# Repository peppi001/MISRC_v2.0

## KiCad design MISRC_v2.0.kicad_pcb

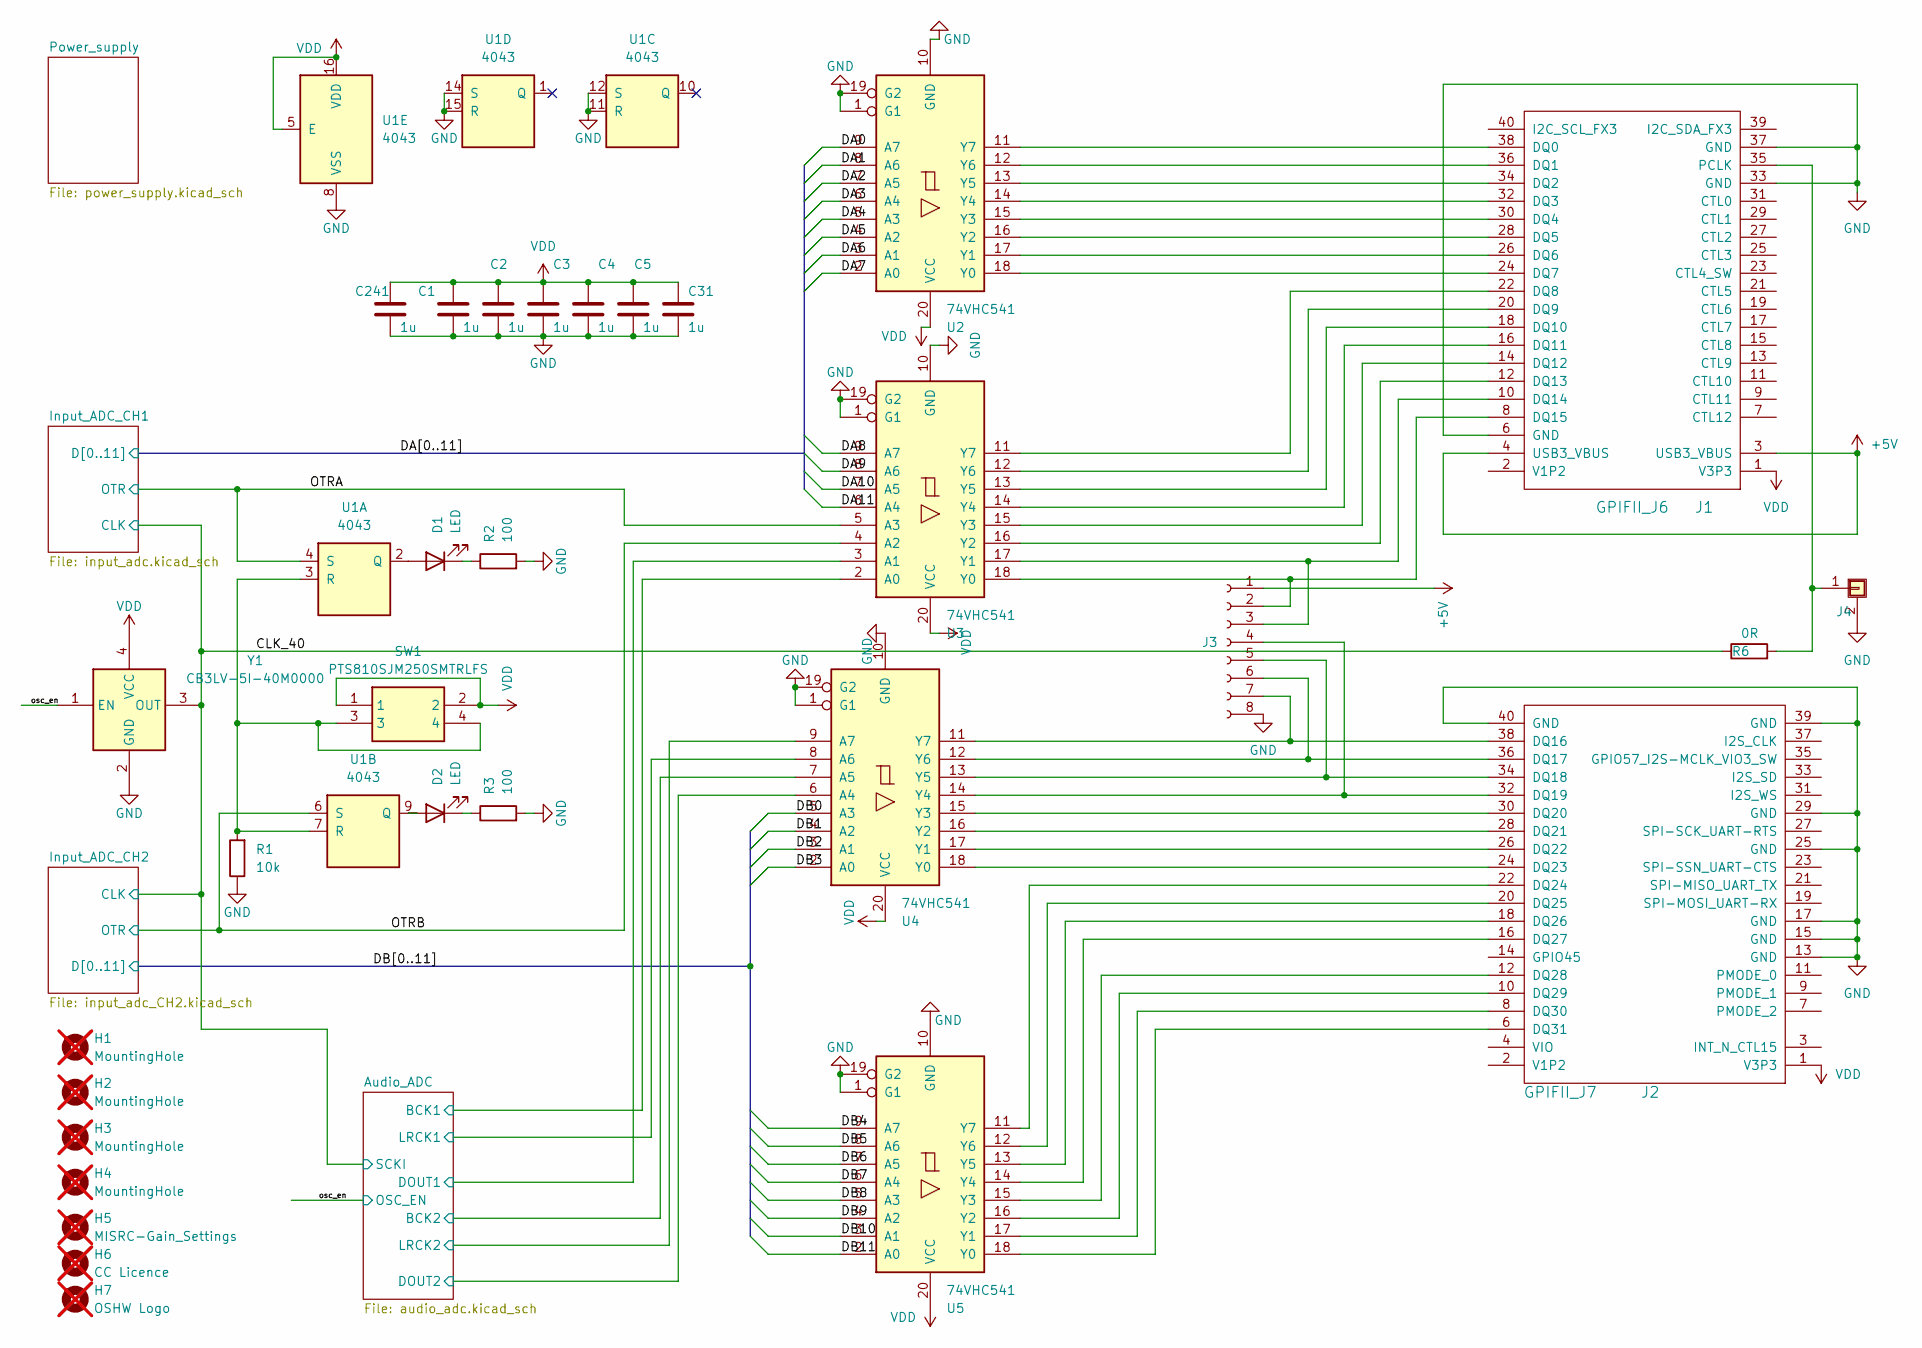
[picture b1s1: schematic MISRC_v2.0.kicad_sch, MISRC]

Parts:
C1, C2, C3, C4, C5, C31, C241: 1u; C_0603_1608Metric; Manufacturer_Part_Number GRM188D71H105KE01D
D1, D2: LED; LED_0805_2012Metric_Pad1.15x1.40mm_HandSolder; Manufacturer_Part_Number APT2012EC
H1, H2, H3, H4: MountingHole; MountingHole_3.2mm_M3; not fitted
H5: MISRC-Gain_Settings; MISRC_gain_settings; not fitted
H6: CC Licence; not fitted
H7: OSHW Logo; OSHW-Logo_5.7x6mm_SilkScreen; not fitted
J1: GPIFII_J6; PinHeader_2x20_P2.54mm_Vertical-1; Manufacturer_Part_Number 61302021121
J2: GPIFII_J7; PinHeader_2x20_P2.54mm_Vertical-1; Manufacturer_Part_Number 61302021121
J3: Conn_01x08_Socket; PinHeader_1x08_P2.54mm_Vertical; Manufacturer_Part_Number 61300811121
J4: Conn_01x01_Shielded; SMA_Amphenol_901-144_Vertical2; Manufacturer_Part_Number RF2-04A-T-00-50-G
R1: 10k; R_0603_1608Metric; Manufacturer_Part_Number RC0603FR-0710KL
R2, R3: 100; R_0603_1608Metric; Manufacturer_Part_Number RC0603FR-07100RL
R6: 0R; R_0603_1608Metric; Manufacturer_Part_Number RC0603FR-070RL
SW1: PTS810SJM250SMTRLFS; PTS810SJG250SMTRLFS; Mouser Part Number 611-PTS810SJM250SMTR
U1: 4043; SO-16_3.9x9.9mm_P1.27mm; Manufacturer_Part_Number HEF4043BT-Q100J
U2, U3, U4, U5: 74VHC541; SOIC-20W_7.5x12.8mm_P1.27mm; Manufacturer_Part_Number 74VHC541D,118
Y1: CB3LV-5I-40M0000; CB3LV5I40M0000; Mouser Part Number 774-CB3LV-5I-40M0000

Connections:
+5V: J1.3 (USB3_VBUS), J1.4 (USB3_VBUS), J3.1; also elsewhere on the board
/Audio_ADC/BCK1: U3.2 (A0); also elsewhere on the board
/Audio_ADC/BCK2: U4.7 (A5); also elsewhere on the board
/Audio_ADC/DOUT1: U3.3 (A1); also elsewhere on the board
/Audio_ADC/DOUT2: U4.6 (A4); also elsewhere on the board
/Audio_ADC/LRCK1: U4.8 (A6); also elsewhere on the board
/Audio_ADC/LRCK2: U4.9 (A7); also elsewhere on the board
/CLK_40: R6.1, Y1.3 (OUT); also elsewhere on the board
/DA0: U2.9 (A7); also elsewhere on the board
/DA1: U2.8 (A6); also elsewhere on the board
/DA2: U2.7 (A5); also elsewhere on the board
/DA3: U2.6 (A4); also elsewhere on the board
/DA4: U2.5 (A3); also elsewhere on the board
/DA5: U2.4 (A2); also elsewhere on the board
/DA6: U2.3 (A1); also elsewhere on the board
/DA7: U2.2 (A0); also elsewhere on the board
/DA8: U3.9 (A7); also elsewhere on the board
/DA9: U3.8 (A6); also elsewhere on the board
/DA10: U3.7 (A5); also elsewhere on the board
/DA11: U3.6 (A4); also elsewhere on the board
/DB0: U4.5 (A3); also elsewhere on the board
/DB1: U4.4 (A2); also elsewhere on the board
/DB2: U4.3 (A1); also elsewhere on the board
/DB3: U4.2 (A0); also elsewhere on the board
/DB4: U5.9 (A7); also elsewhere on the board
/DB5: U5.8 (A6); also elsewhere on the board
/DB6: U5.7 (A5); also elsewhere on the board
/DB7: U5.6 (A4); also elsewhere on the board
/DB8: U5.5 (A3); also elsewhere on the board
/DB9: U5.4 (A2); also elsewhere on the board
/DB10: U5.3 (A1); also elsewhere on the board
/DB11: U5.2 (A0); also elsewhere on the board
/OTRA: U1.4 (S), U3.5 (A3); also elsewhere on the board
/OTRB: U1.6 (S), U3.4 (A2); also elsewhere on the board
/osc_en: Y1.1 (EN); also elsewhere on the board
GND: C1.2, C2.2, C3.2, C4.2, C5.2, C31.2, C241.2, J1.6 (GND), J1.33 (GND), J1.37 (GND), J2.13 (GND), J2.15 (GND), J2.17 (GND), J2.25 (GND), J2.29 (GND), J2.39 (GND), J2.40 (GND), J3.8, J4.2 (Shield), R1.1, R2.2, R3.2, U1.8 (VSS), U1.11 (R), U1.12 (S), U1.14 (S), U1.15 (R), U2.1 (G1), U2.10 (GND), U2.19 (G2), U3.1 (G1), U3.10 (GND), U3.19 (G2), U4.1 (G1), U4.10 (GND), U4.19 (G2), U5.1 (G1), U5.10 (GND), U5.19 (G2), Y1.2 (GND); also elsewhere on the board
unnamed: D1.2 (A), U1.2 (Q)
unnamed: D1.1 (K), R2.1
unnamed: D2.2 (A), U1.9 (Q)
unnamed: D2.1 (K), R3.1
unnamed: J1.38 (DQ0), U2.11 (Y7)
unnamed: J1.36 (DQ1), U2.12 (Y6)
unnamed: J1.34 (DQ2), U2.13 (Y5)
unnamed: J1.32 (DQ3), U2.14 (Y4)
unnamed: J1.30 (DQ4), U2.15 (Y3)
unnamed: J1.28 (DQ5), U2.16 (Y2)
unnamed: J1.26 (DQ6), U2.17 (Y1)
unnamed: J1.24 (DQ7), U2.18 (Y0)
unnamed: J1.22 (DQ8), U3.11 (Y7)
unnamed: J1.20 (DQ9), U3.12 (Y6)
unnamed: J1.18 (DQ10), U3.13 (Y5)
unnamed: J1.16 (DQ11), U3.14 (Y4)
unnamed: J1.14 (DQ12), U3.15 (Y3)
unnamed: J1.12 (DQ13), U3.16 (Y2)
unnamed: J1.10 (DQ14), J3.3, U3.17 (Y1)
unnamed: J1.8 (DQ15), J3.2, U3.18 (Y0)
unnamed: J1.35 (PCLK), J4.1, R6.2
unnamed: J2.38 (DQ16), J3.7, U4.11 (Y7)
unnamed: J2.36 (DQ17), J3.6, U4.12 (Y6)
unnamed: J2.34 (DQ18), J3.5, U4.13 (Y5)
unnamed: J2.32 (DQ19), J3.4, U4.14 (Y4)
unnamed: J2.30 (DQ20), U4.15 (Y3)
unnamed: J2.28 (DQ21), U4.16 (Y2)
unnamed: J2.26 (DQ22), U4.17 (Y1)
unnamed: J2.24 (DQ23), U4.18 (Y0)
unnamed: J2.22 (DQ24), U5.11 (Y7)
unnamed: J2.20 (DQ25), U5.12 (Y6)
unnamed: J2.18 (DQ26), U5.13 (Y5)
unnamed: J2.16 (DQ27), U5.14 (Y4)
unnamed: J2.12 (DQ28), U5.15 (Y3)
unnamed: J2.10 (DQ29), U5.16 (Y2)
unnamed: J2.8 (DQ30), U5.17 (Y1)
unnamed: J2.6 (DQ31), U5.18 (Y0)
unnamed: R1.2, SW1.3, SW1.4, U1.3 (R), U1.7 (R)
VDD: C1.1, C2.1, C3.1, C4.1, C5.1, C31.1, C241.1, J1.1 (V3P3), J2.1 (V3P3), SW1.1, SW1.2, U1.5 (E), U1.16 (VDD), U2.20 (VCC), U3.20 (VCC), U4.20 (VCC), U5.20 (VCC), Y1.4 (VCC); also elsewhere on the board

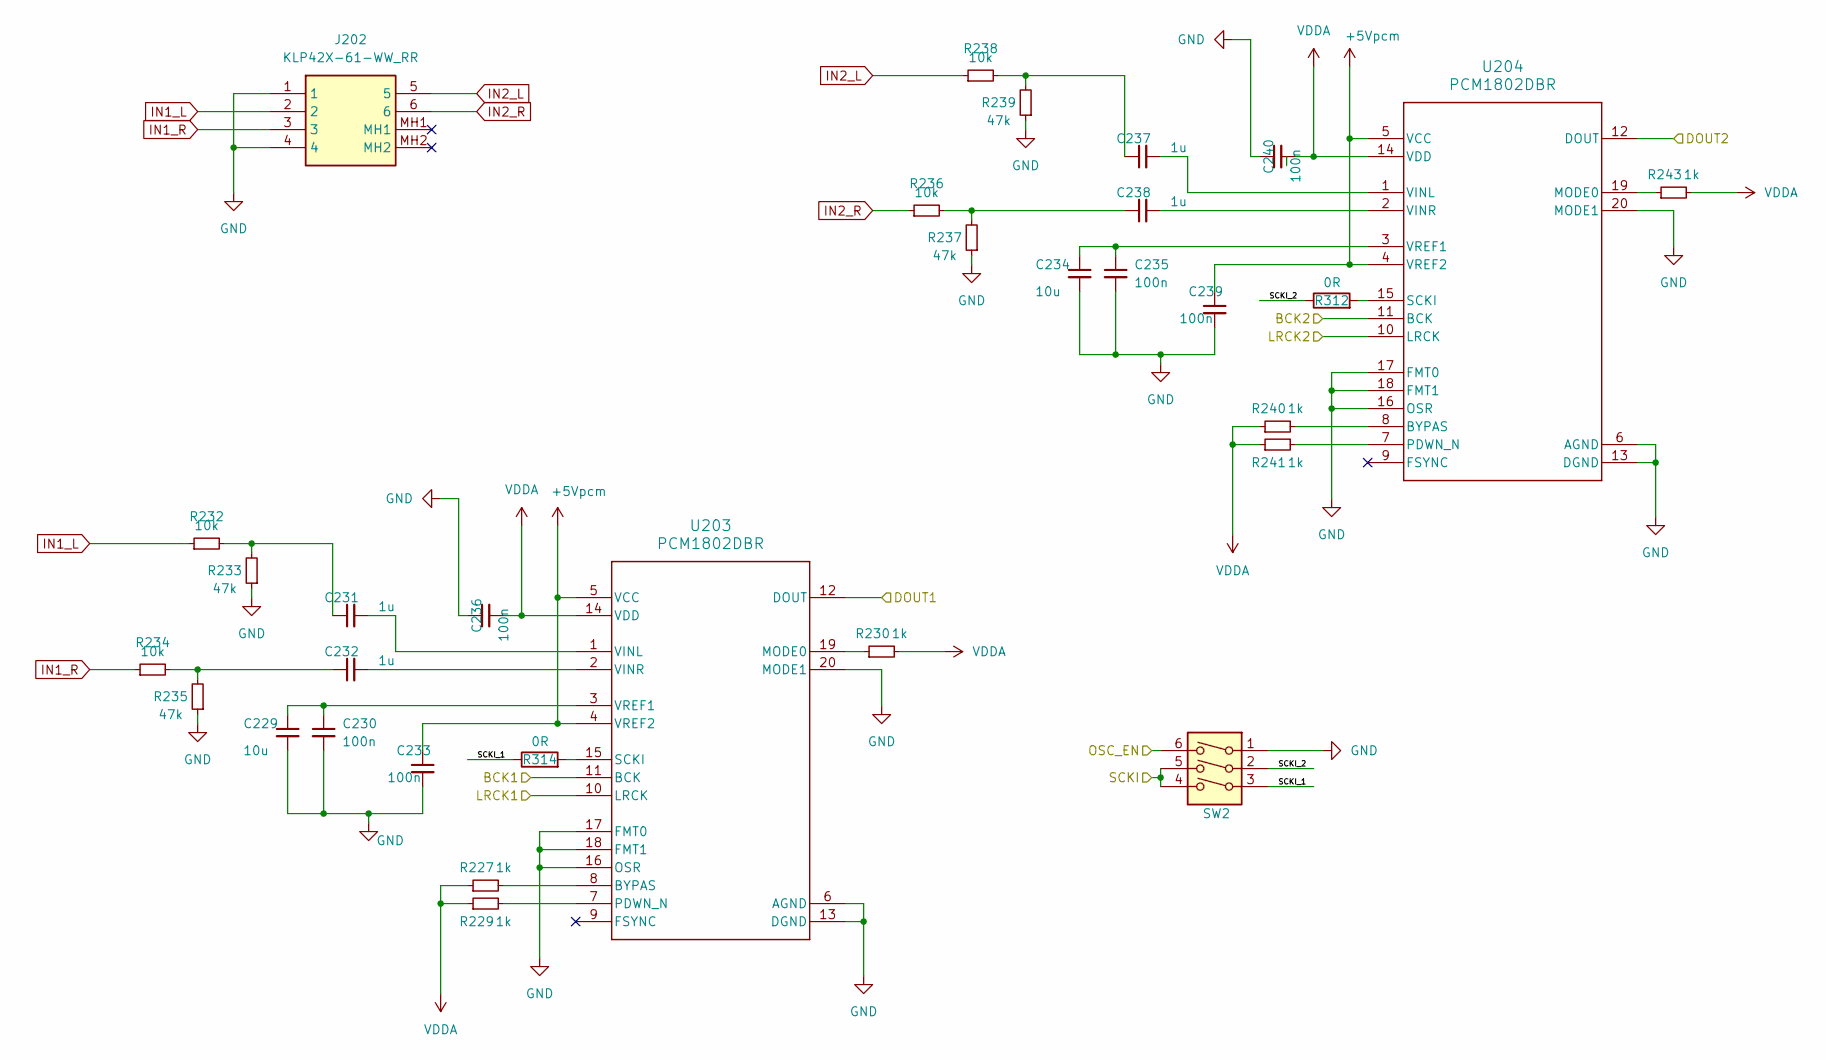
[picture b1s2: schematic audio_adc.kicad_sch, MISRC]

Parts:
C229, C234: 10u; C_0603_1608Metric; Manufacturer_Part_Number GRM188C81C106MA73D
C230, C233, C235, C236, C239, C240: 100n; C_0603_1608Metric; Manufacturer_Part_Number GRM188R72A104KA35D
C231, C232, C237, C238: 1u; C_0603_1608Metric; Manufacturer_Part_Number GRM188D71H105KE01D
J202: KLP42X-61-WW_RR; KLP42X61WWRR; Mouser Part Number 806-KLP42X-61-WWRR
R227, R229, R230, R240, R241, R243: 1k; R_0603_1608Metric; Manufacturer_Part_Number RC0603FR-071KL
R232, R234, R236, R238: 10k; R_0603_1608Metric; Manufacturer_Part_Number RC0603FR-0710KL
R233, R235, R237, R239: 47k; R_0603_1608Metric; Manufacturer_Part_Number RC0603FR-0747KL
R312, R314: 0R; R_0603_1608Metric; Manufacturer_Part_Number RC0603FR-070RL
SW2: SW_DIP_x03; SW_DIP_SPSTx03_Slide_6.7x9.18mm_W8.61mm_P2.54mm_LowProfile; Manufacturer_Part_Number A6S-3104-H
U203, U204: PCM1802DBR; SOP65P780X200-20N; Manufacturer_Part_Number PCM1802DBR

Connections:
+5Vpcm: C233.1, C239.1, U203.4 (VREF2), U203.5 (VCC), U204.4 (VREF2), U204.5 (VCC); also elsewhere on the board
/Audio_ADC/BCK1: U203.11 (BCK); also elsewhere on the board
/Audio_ADC/BCK2: U204.11 (BCK); also elsewhere on the board
/Audio_ADC/DOUT1: U203.12 (DOUT); also elsewhere on the board
/Audio_ADC/DOUT2: U204.12 (DOUT); also elsewhere on the board
/Audio_ADC/LRCK1: U203.10 (LRCK); also elsewhere on the board
/Audio_ADC/LRCK2: U204.10 (LRCK); also elsewhere on the board
/Audio_ADC/SCKI_1: R314.1, SW2.3
/Audio_ADC/SCKI_2: R312.1, SW2.2
/CLK_40: SW2.4, SW2.5; also elsewhere on the board
/osc_en: SW2.6; also elsewhere on the board
GND: C229.2, C230.2, C233.2, C234.2, C235.2, C236.1, C239.2, C240.1, J202.1, J202.4, R233.1, R235.1, R237.1, R239.1, SW2.1, U203.6 (AGND), U203.13 (DGND), U203.16 (OSR), U203.17 (FMT0), U203.18 (FMT1), U203.20 (MODE1), U204.6 (AGND), U204.13 (DGND), U204.16 (OSR), U204.17 (FMT0), U204.18 (FMT1), U204.20 (MODE1); also elsewhere on the board
IN1_L: J202.2, R232.1
IN1_R: J202.3, R234.1
IN2_L: J202.5, R238.1
IN2_R: J202.6, R236.1
unnamed: C231.1, R232.2, R233.2
unnamed: C232.1, R234.2, R235.2
unnamed: C237.1, R238.2, R239.2
unnamed: C238.1, R236.2, R237.2
unnamed: R227.2, U203.8 (BYPAS)
unnamed: R230.1, U203.19 (MODE0)
unnamed: R229.2, U203.7 (PDWN_N)
unnamed: R314.2, U203.15 (SCKI)
unnamed: C231.2, U203.1 (VINL)
unnamed: C232.2, U203.2 (VINR)
unnamed: C229.1, C230.1, U203.3 (VREF1)
unnamed: R240.2, U204.8 (BYPAS)
unnamed: R243.1, U204.19 (MODE0)
unnamed: R241.2, U204.7 (PDWN_N)
unnamed: R312.2, U204.15 (SCKI)
unnamed: C237.2, U204.1 (VINL)
unnamed: C238.2, U204.2 (VINR)
unnamed: C234.1, C235.1, U204.3 (VREF1)
VDDA: C236.2, C240.2, R227.1, R229.1, R230.2, R240.1, R241.1, R243.2, U203.14 (VDD), U204.14 (VDD); also elsewhere on the board

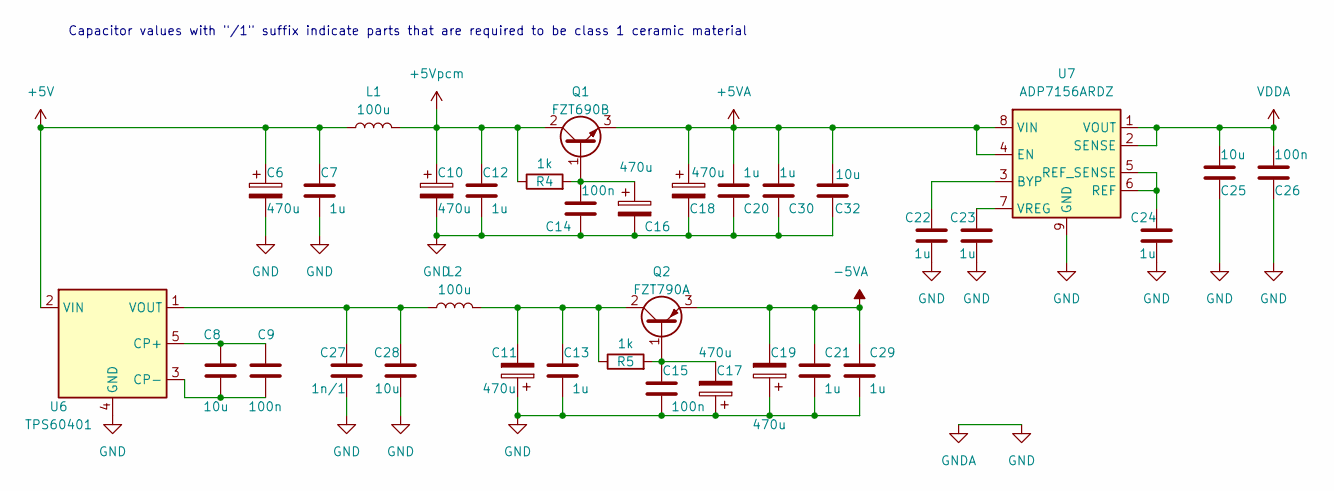
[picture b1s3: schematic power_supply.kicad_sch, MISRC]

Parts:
C6, C10, C11, C16, C17, C18, C19: 470u; CAPAE1030X850N; Manufacturer_Part_Number UCL1C471MCL6GS
C7, C12, C13, C20, C21, C22, C23, C24, C29, C30: 1u; C_0603_1608Metric; Manufacturer_Part_Number GRM188D71H105KE01D
C8, C25, C28, C32: 10u; C_0603_1608Metric; Manufacturer_Part_Number GRM188C81C106MA73D
C9, C14, C15, C26: 100n; C_0603_1608Metric; Manufacturer_Part_Number GRM188R72A104KA35D
C27: 1n/1; C_0603_1608Metric; Manufacturer_Part_Number GCM1885C1H102FA16D
L1, L2: 100u; L_Bourns-SRU8043_2; Manufacturer_Part_Number SRU8043-101Y
Q1: FZT690B; SOT-223-3_TabPin2; Manufacturer_Part_Number FZT690BTA
Q2: FZT790A; SOT-223-3_TabPin2; Manufacturer_Part_Number FZT790A
R4, R5: 1k; R_0603_1608Metric; Manufacturer_Part_Number RC0603FR-071KL
U6: TPS60401; SOT-23-5; Manufacturer_Part_Number TPS60401DBVT
U7: ADP7156ARDZ; SOIC-8-1EP_3.9x4.9mm_P1.27mm_EP2.29x3mm_2; Manufacturer_Part_Number ADP7156ARDZ-3.3-R7

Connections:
+5V: C6.1, C7.1, L1.1, U6.2 (VIN); also elsewhere on the board
+5VA: C18.1, C20.1, C30.1, C32.2, Q1.3 (E), U7.4 (EN), U7.8 (VIN); also elsewhere on the board
+5Vpcm: C10.1, C12.1, L1.2, Q1.2 (C), R4.1; also elsewhere on the board
-5VA: C19.2, C21.1, C29.1, Q2.3 (E); also elsewhere on the board
GND: C6.2, C7.2, C10.2, C11.1, C12.2, C13.2, C14.2, C15.2, C16.2, C17.1, C18.2, C19.1, C20.2, C21.2, C22.1, C23.1, C24.2, C25.2, C26.2, C27.1, C28.1, C29.2, C30.2, C32.1, U6.4 (GND), U7.9 (GND); also elsewhere on the board
unnamed: C14.1, C16.1, Q1.1 (B), R4.2
unnamed: C15.1, C17.2, Q2.1 (B), R5.2
unnamed: C11.2, C13.1, L2.2, Q2.2 (C), R5.1
unnamed: C8.1, C9.1, U6.5 (CP+)
unnamed: C8.2, C9.2, U6.3 (CP-)
unnamed: C27.2, C28.2, L2.1, U6.1 (VOUT)
unnamed: C22.2, U7.3 (BYP)
unnamed: C24.1, U7.5 (REF_SENSE), U7.6 (REF)
unnamed: C23.2, U7.7 (VREG)
VDDA: C25.1, C26.1, U7.1 (VOUT), U7.2 (SENSE); also elsewhere on the board

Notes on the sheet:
Capacitor values with "/1" suffix indicate parts that are required to be class 1 ceramic material

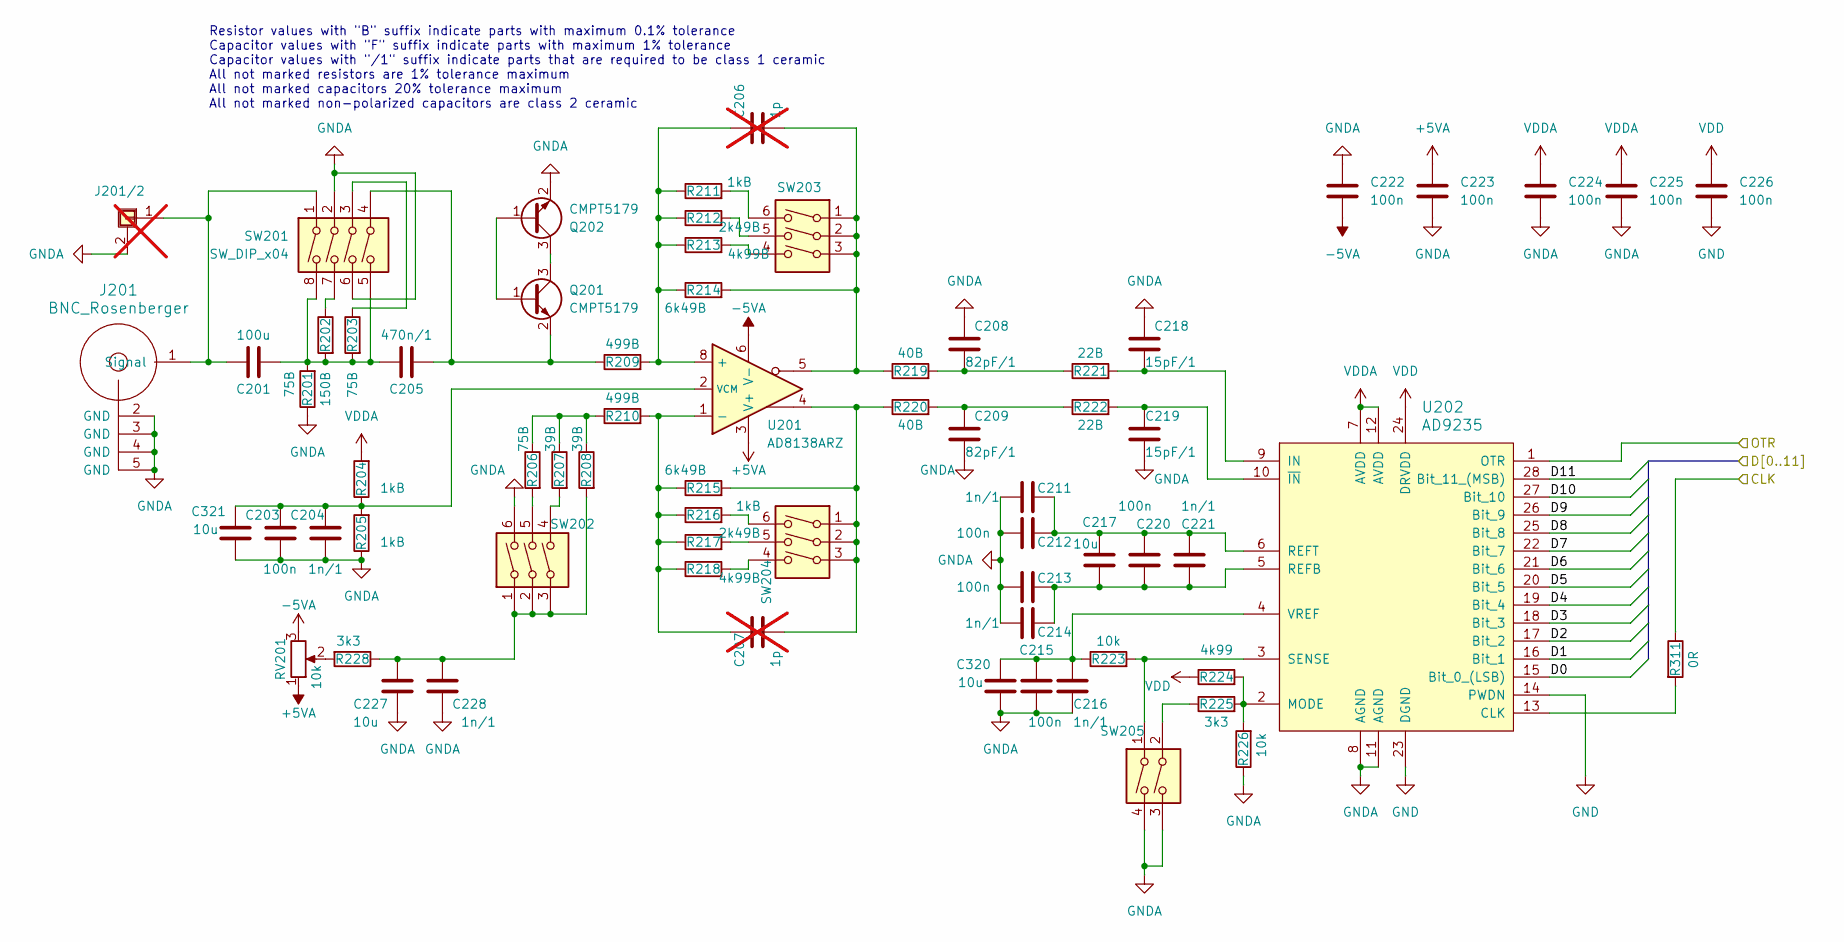
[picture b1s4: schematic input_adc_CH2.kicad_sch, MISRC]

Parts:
C201: 100u; C_1210_3225Metric; Manufacturer_Part_Number GRM32ER61A107ME20K
C203, C212, C213, C215, C220, C222, C223, C224, C225, C226: 100n; C_0603_1608Metric; Manufacturer_Part_Number GRM188R72A104KA35D
C204, C211, C214, C216, C221, C228: 1n/1; C_0603_1608Metric; Manufacturer_Part_Number GCM1885C1H102FA16D
C205: 470n/1; C_0603_1608Metric; Manufacturer_Part_Number GRM188R71E474KA12D
C206, C207: 1p; C_0603_1608Metric; not fitted
C208, C209: 82pF/1; C_0603_1608Metric; Manufacturer_Part_Number GRM1885C1H820GA01D
C217, C227, C320, C321: 10u; C_0603_1608Metric; Manufacturer_Part_Number GRM188C81C106MA73D
C218, C219: 15pF/1; C_0603_1608Metric; Manufacturer_Part_Number GRM1885C1H150JA01J
J201: BNC_Rosenberger; BNC_Right_Angle-DOSIN-801-0050_5pin; Manufacturer_Part_Number DOSIN-801-0050
J201/2: Conn_01x01_Shielded; SMA_Amphenol_901-144_Horizontal; Manufacturer_Part_Number CONSMA002-L-G; not fitted
Q201, Q202: CMPT5179; SOT-23; Manufacturer_Part_Number CMPT5179 TR PBFREE
R201, R203, R206: 75B; R_0603_1608Metric; Manufacturer_Part_Number RC0603FR-1075RL
R202: 150B; R_0603_1608Metric; Manufacturer_Part_Number RC0603FR-07150RL
R204, R205, R211, R216: 1kB; R_0603_1608Metric; Manufacturer_Part_Number RC0603FR-071KL
R207, R208: 39B; R_0603_1608Metric; Manufacturer_Part_Number RC0603FR-0739RL
R209, R210: 499B; R_0603_1608Metric; Manufacturer_Part_Number RC0603FR-07499RL
R212, R217: 2k49B; R_0603_1608Metric; Manufacturer_Part_Number RC0603FR-072K49L
R213, R218: 4k99B; R_0603_1608Metric; Manufacturer_Part_Number RC0603FR-074K99L
R214, R215: 6k49B; R_0603_1608Metric; Manufacturer_Part_Number RC0603FR-136K49L
R219, R220: 40B; R_0603_1608Metric; Manufacturer_Part_Number RC0603FR-0739R2L
R221, R222: 22B; R_0603_1608Metric; Manufacturer_Part_Number RC0603FR-0722RL
R223, R226: 10k; R_0603_1608Metric; Manufacturer_Part_Number RC0603FR-0710KL
R224: 4k99; R_0603_1608Metric; Manufacturer_Part_Number RC0603FR-074K99L
R225, R228: 3k3; R_0603_1608Metric; Manufacturer_Part_Number RC0603FR-133K3L
R311: 0R; R_0603_1608Metric; Manufacturer_Part_Number RC0603FR-070RL
RV201: 10k; Potentiometer_Bourns_3266W_Vertical; Manufacturer_Part_Number 3266W-1-103LF
SW201: SW_DIP_x04; SW_DIP_SPSTx04_Slide_6.7x11.72mm_W8.61mm_P2.54mm_LowProfile; Manufacturer_Part_Number IKD0403101
SW202, SW203, SW204: SW_DIP_x03; SW_DIP_SPSTx03_Slide_6.7x9.18mm_W8.61mm_P2.54mm_LowProfile; Manufacturer_Part_Number A6S-3104-H
SW205: SW_DIP_x02; SW_DIP_SPSTx02_Slide_6.7x6.64mm_W8.61mm_P2.54mm_LowProfile; Manufacturer_Part_Number IKD0203101
U201: AD8138ARZ; SO-8_3.9x4.9mm_P1.27mm; Manufacturer_Part_Number AD8138ARZ
U202: AD9235; TSSOP-28_4.4x9.7mm_P0.65mm; Manufacturer_Part_Number AD9235BRUZ-40

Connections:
+5VA: C223.1, RV201.1, U201.3 (V+); also elsewhere on the board
-5VA: C222.2, RV201.3, U201.6 (V-); also elsewhere on the board
/CLK_40: R311.1; also elsewhere on the board
/DB0: U202.15 (Bit_0_(LSB)); also elsewhere on the board
/DB1: U202.16 (Bit_1); also elsewhere on the board
/DB2: U202.17 (Bit_2); also elsewhere on the board
/DB3: U202.18 (Bit_3); also elsewhere on the board
/DB4: U202.19 (Bit_4); also elsewhere on the board
/DB5: U202.20 (Bit_5); also elsewhere on the board
/DB6: U202.21 (Bit_6); also elsewhere on the board
/DB7: U202.22 (Bit_7); also elsewhere on the board
/DB8: U202.25 (Bit_8); also elsewhere on the board
/DB9: U202.26 (Bit_9); also elsewhere on the board
/DB10: U202.27 (Bit_10); also elsewhere on the board
/DB11: U202.28 (Bit_11_(MSB)); also elsewhere on the board
/OTRB: U202.1 (OTR); also elsewhere on the board
GND: C203.2, C204.2, C208.1, C209.2, C211.1, C212.1, C213.1, C214.1, C215.2, C216.2, C218.1, C219.2, C222.1, C223.2, C224.2, C225.2, C226.2, C227.2, C228.2, C320.2, C321.2, J201.2 (GND), J201.3 (GND), J201.4 (GND), J201.5 (GND), J201/2.2 (Shield), Q202.2 (E), R201.1, R205.1, R226.1, SW201.2, SW201.6, SW202.6, SW205.3, SW205.4, U202.8 (AGND), U202.11 (AGND), U202.14 (PWDN), U202.23 (DGND); also elsewhere on the board
unnamed: C201.2, C205.1, R201.2, R202.2, R203.2, SW201.5, SW201.8
unnamed: C206.2, R214.2, R219.1, SW203.1, SW203.2, SW203.3, U201.5
unnamed: C207.2, R215.2, R220.1, SW204.1, SW204.2, SW204.3, U201.4
unnamed: C208.2, R219.2, R221.1
unnamed: C209.1, R220.2, R222.1
unnamed: C227.1, C228.1, R208.2, R228.1, SW202.1, SW202.2, SW202.3
unnamed: C201.1, J201.1 (Signal), J201/2.1, SW201.1
unnamed: Q201.1 (B), Q202.1 (B)
unnamed: Q201.3 (C), Q202.3 (C)
unnamed: C205.2, Q201.2 (E), R209.1, SW201.4
unnamed: R202.1, SW201.7
unnamed: R203.1, SW201.3
unnamed: R206.1, R207.1, R208.1, R210.1
unnamed: R206.2, SW202.5
unnamed: R207.2, SW202.4
unnamed: R211.2, SW203.6
unnamed: R212.2, SW203.5
unnamed: R213.2, SW203.4
unnamed: R216.2, SW204.6
unnamed: R217.2, SW204.5
unnamed: R218.2, SW204.4
unnamed: R225.1, SW205.2
unnamed: R228.2, RV201.2
unnamed: C206.1, R209.2, R211.1, R212.1, R213.1, R214.1, U201.8 (+)
unnamed: C207.1, R210.2, R215.1, R216.1, R217.1, R218.1, U201.1 (-)
unnamed: C203.1, C204.1, C321.1, R204.1, R205.2, U201.2 (VCM)
unnamed: R311.2, U202.13 (CLK)
unnamed: C218.2, R221.2, U202.9 (IN)
unnamed: R224.2, R225.2, R226.2, U202.2 (MODE)
unnamed: C213.2, C214.2, C217.2, C220.2, C221.2, U202.5 (REFB)
unnamed: C211.2, C212.2, C217.1, C220.1, C221.1, U202.6 (REFT)
unnamed: R223.2, SW205.1, U202.3 (SENSE)
unnamed: C215.1, C216.1, C320.1, R223.1, U202.4 (VREF)
unnamed: C219.1, R222.2, U202.10 (~IN)
VDD: C226.1, R224.1, U202.24 (DRVDD); also elsewhere on the board
VDDA: C224.1, C225.1, R204.2, U202.7 (AVDD), U202.12 (AVDD); also elsewhere on the board

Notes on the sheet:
Resistor values with "B" suffix indicate parts with maximum 0.1% tolerance Capacitor values with "F" suffix indicate parts with maximum 1% tolerance Capacitor values with "/1" suffix indicate parts that are required to be class 1 ceramic All not marked resistors are 1% tolerance maximum All not mar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

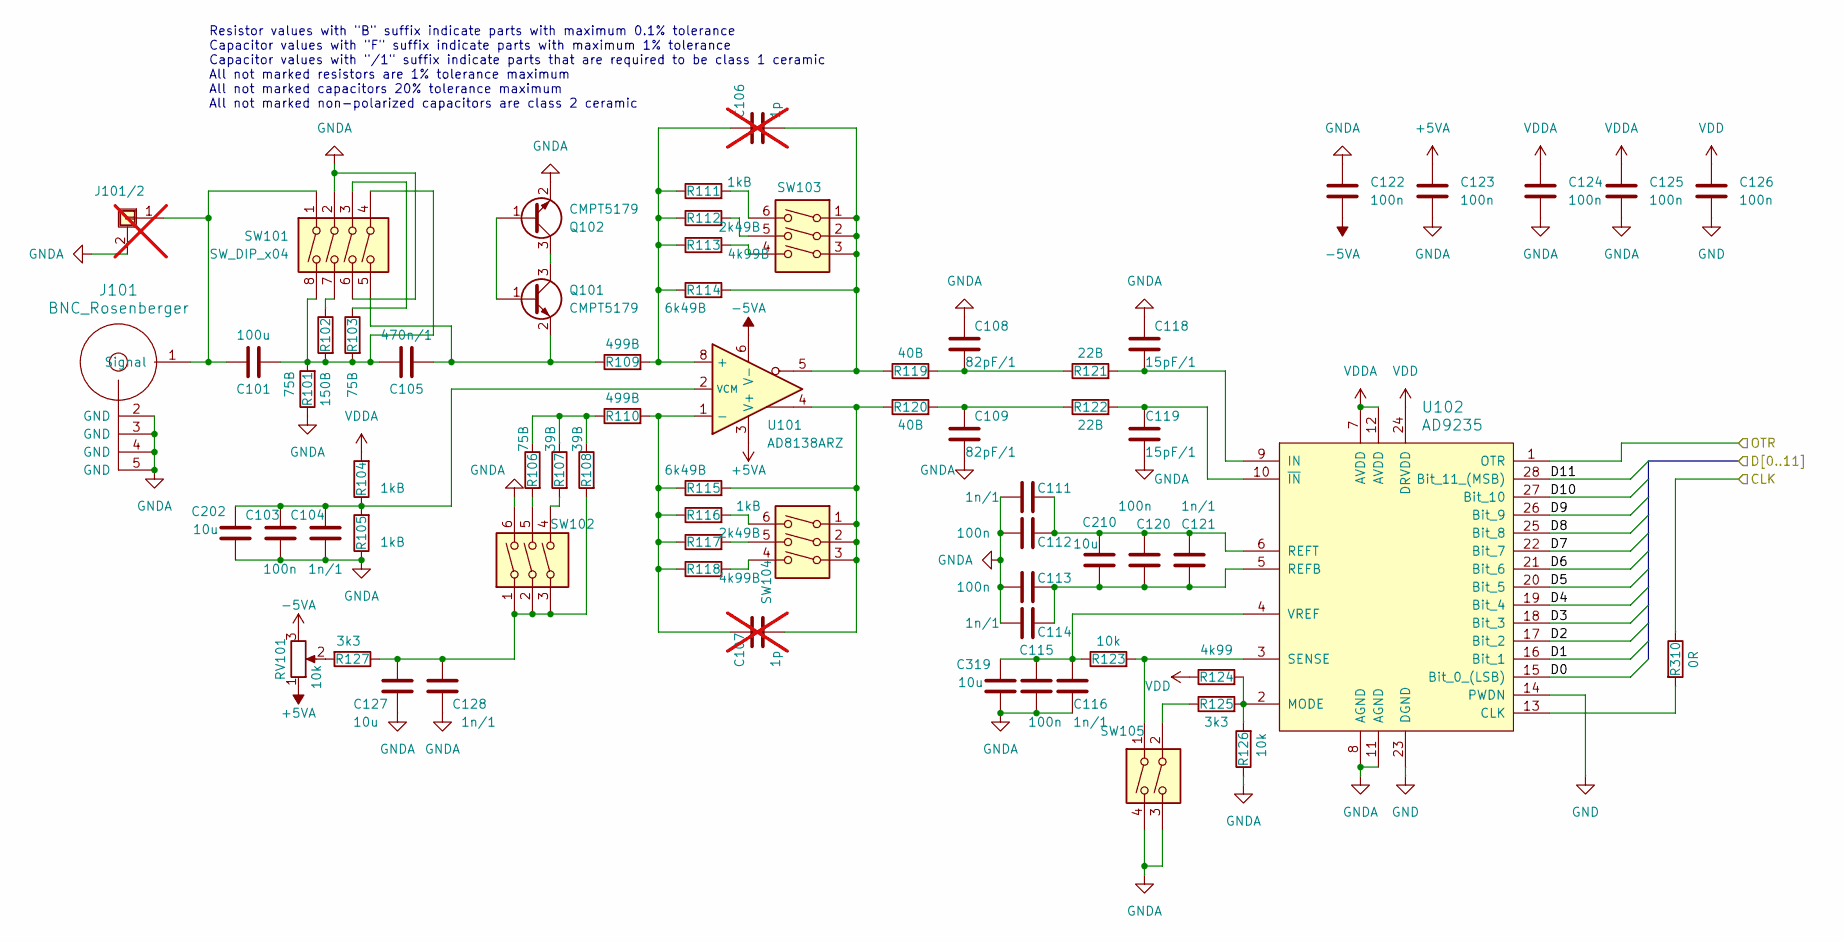
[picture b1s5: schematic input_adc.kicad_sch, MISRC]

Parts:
C101: 100u; C_1210_3225Metric; Manufacturer_Part_Number GRM32ER61A107ME20K
C103, C112, C113, C115, C120, C122, C123, C124, C125, C126: 100n; C_0603_1608Metric; Manufacturer_Part_Number GRM188R72A104KA35D
C104, C111, C114, C116, C121, C128: 1n/1; C_0603_1608Metric; Manufacturer_Part_Number GCM1885C1H102FA16D
C105: 470n/1; C_0603_1608Metric; Manufacturer_Part_Number GRM188R71E474KA12D
C106, C107: 1p; C_0603_1608Metric; not fitted
C108, C109: 82pF/1; C_0603_1608Metric; Manufacturer_Part_Number GRM1885C1H820GA01D
C118, C119: 15pF/1; C_0603_1608Metric; Manufacturer_Part_Number GRM1885C1H150JA01J
C127, C202, C210, C319: 10u; C_0603_1608Metric; Manufacturer_Part_Number GRM188C81C106MA73D
J101: BNC_Rosenberger; BNC_Right_Angle-DOSIN-801-0050_5pin; Manufacturer_Part_Number DOSIN-801-0050
J101/2: Conn_01x01_Shielded; SMA_Amphenol_901-144_Horizontal; Manufacturer_Part_Number CONSMA002-L-G; not fitted
Q101, Q102: CMPT5179; SOT-23; Manufacturer_Part_Number CMPT5179 TR PBFREE
R101, R103, R106: 75B; R_0603_1608Metric; Manufacturer_Part_Number RC0603FR-1075RL
R102: 150B; R_0603_1608Metric; Manufacturer_Part_Number RC0603FR-07150RL
R104, R105, R111, R116: 1kB; R_0603_1608Metric; Manufacturer_Part_Number RC0603FR-071KL
R107, R108: 39B; R_0603_1608Metric; Manufacturer_Part_Number RC0603FR-0739RL
R109, R110: 499B; R_0603_1608Metric; Manufacturer_Part_Number RC0603FR-07499RL
R112, R117: 2k49B; R_0603_1608Metric; Manufacturer_Part_Number RC0603FR-072K49L
R113, R118: 4k99B; R_0603_1608Metric; Manufacturer_Part_Number RC0603FR-074K99L
R114, R115: 6k49B; R_0603_1608Metric; Manufacturer_Part_Number RC0603FR-136K49L
R119, R120: 40B; R_0603_1608Metric; Manufacturer_Part_Number RC0603FR-0739R2L
R121, R122: 22B; R_0603_1608Metric; Manufacturer_Part_Number RC0603FR-0722RL
R123, R126: 10k; R_0603_1608Metric; Manufacturer_Part_Number RC0603FR-0710KL
R124: 4k99; R_0603_1608Metric; Manufacturer_Part_Number RC0603FR-074K99L
R125, R127: 3k3; R_0603_1608Metric; Manufacturer_Part_Number RC0603FR-133K3L
R310: 0R; R_0603_1608Metric; Manufacturer_Part_Number RC0603FR-070RL
RV101: 10k; Potentiometer_Bourns_3266W_Vertical; Manufacturer_Part_Number 3266W-1-103LF
SW101: SW_DIP_x04; SW_DIP_SPSTx04_Slide_6.7x11.72mm_W8.61mm_P2.54mm_LowProfile; Manufacturer_Part_Number IKD0403101
SW102, SW103, SW104: SW_DIP_x03; SW_DIP_SPSTx03_Slide_6.7x9.18mm_W8.61mm_P2.54mm_LowProfile; Manufacturer_Part_Number A6S-3104-H
SW105: SW_DIP_x02; SW_DIP_SPSTx02_Slide_6.7x6.64mm_W8.61mm_P2.54mm_LowProfile; Manufacturer_Part_Number IKD0203101
U101: AD8138ARZ; SO-8_3.9x4.9mm_P1.27mm; Manufacturer_Part_Number AD8138ARZ
U102: AD9235; TSSOP-28_4.4x9.7mm_P0.65mm; Manufacturer_Part_Number AD9235BRUZ-40

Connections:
+5VA: C123.1, RV101.1, U101.3 (V+); also elsewhere on the board
-5VA: C122.2, RV101.3, U101.6 (V-); also elsewhere on the board
/CLK_40: R310.1; also elsewhere on the board
/DA0: U102.15 (Bit_0_(LSB)); also elsewhere on the board
/DA1: U102.16 (Bit_1); also elsewhere on the board
/DA2: U102.17 (Bit_2); also elsewhere on the board
/DA3: U102.18 (Bit_3); also elsewhere on the board
/DA4: U102.19 (Bit_4); also elsewhere on the board
/DA5: U102.20 (Bit_5); also elsewhere on the board
/DA6: U102.21 (Bit_6); also elsewhere on the board
/DA7: U102.22 (Bit_7); also elsewhere on the board
/DA8: U102.25 (Bit_8); also elsewhere on the board
/DA9: U102.26 (Bit_9); also elsewhere on the board
/DA10: U102.27 (Bit_10); also elsewhere on the board
/DA11: U102.28 (Bit_11_(MSB)); also elsewhere on the board
/OTRA: U102.1 (OTR); also elsewhere on the board
GND: C103.2, C104.2, C108.1, C109.2, C111.1, C112.1, C113.1, C114.1, C115.2, C116.2, C118.1, C119.2, C122.1, C123.2, C124.2, C125.2, C126.2, C127.2, C128.2, C202.2, C319.2, J101.2 (GND), J101.3 (GND), J101.4 (GND), J101.5 (GND), J101/2.2 (Shield), Q102.2 (E), R101.1, R105.1, R126.1, SW101.2, SW101.6, SW102.6, SW105.3, SW105.4, U102.8 (AGND), U102.11 (AGND), U102.14 (PWDN), U102.23 (DGND); also elsewhere on the board
unnamed: C101.2, C105.1, R101.2, R102.2, R103.2, SW101.4, SW101.8
unnamed: C106.2, R114.2, R119.1, SW103.1, SW103.2, SW103.3, U101.5
unnamed: C107.2, R115.2, R120.1, SW104.1, SW104.2, SW104.3, U101.4
unnamed: C108.2, R119.2, R121.1
unnamed: C109.1, R120.2, R122.1
unnamed: C127.1, C128.1, R108.2, R127.1, SW102.1, SW102.2, SW102.3
unnamed: C101.1, J101.1 (Signal), J101/2.1, SW101.1
unnamed: Q101.1 (B), Q102.1 (B)
unnamed: Q101.3 (C), Q102.3 (C)
unnamed: C105.2, Q101.2 (E), R109.1, SW101.5
unnamed: R102.1, SW101.7
unnamed: R103.1, SW101.3
unnamed: R106.1, R107.1, R108.1, R110.1
unnamed: R106.2, SW102.5
unnamed: R107.2, SW102.4
unnamed: R111.2, SW103.6
unnamed: R112.2, SW103.5
unnamed: R113.2, SW103.4
unnamed: R116.2, SW104.6
unnamed: R117.2, SW104.5
unnamed: R118.2, SW104.4
unnamed: R125.1, SW105.2
unnamed: R127.2, RV101.2
unnamed: C106.1, R109.2, R111.1, R112.1, R113.1, R114.1, U101.8 (+)
unnamed: C107.1, R110.2, R115.1, R116.1, R117.1, R118.1, U101.1 (-)
unnamed: C103.1, C104.1, C202.1, R104.1, R105.2, U101.2 (VCM)
unnamed: R310.2, U102.13 (CLK)
unnamed: C118.2, R121.2, U102.9 (IN)
unnamed: R124.2, R125.2, R126.2, U102.2 (MODE)
unnamed: C113.2, C114.2, C120.2, C121.2, C210.2, U102.5 (REFB)
unnamed: C111.2, C112.2, C120.1, C121.1, C210.1, U102.6 (REFT)
unnamed: R123.2, SW105.1, U102.3 (SENSE)
unnamed: C115.1, C116.1, C319.1, R123.1, U102.4 (VREF)
unnamed: C119.1, R122.2, U102.10 (~IN)
VDD: C126.1, R124.1, U102.24 (DRVDD); also elsewhere on the board
VDDA: C124.1, C125.1, R104.2, U102.7 (AVDD), U102.12 (AVDD); also elsewhere on the board

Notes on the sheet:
Resistor values with "B" suffix indicate parts with maximum 0.1% tolerance Capacitor values with "F" suffix indicate parts with maximum 1% tolerance Capacitor values with "/1" suffix indicate parts that are required to be class 1 ceramic All not marked resistors are 1% tolerance maximum All not mar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
